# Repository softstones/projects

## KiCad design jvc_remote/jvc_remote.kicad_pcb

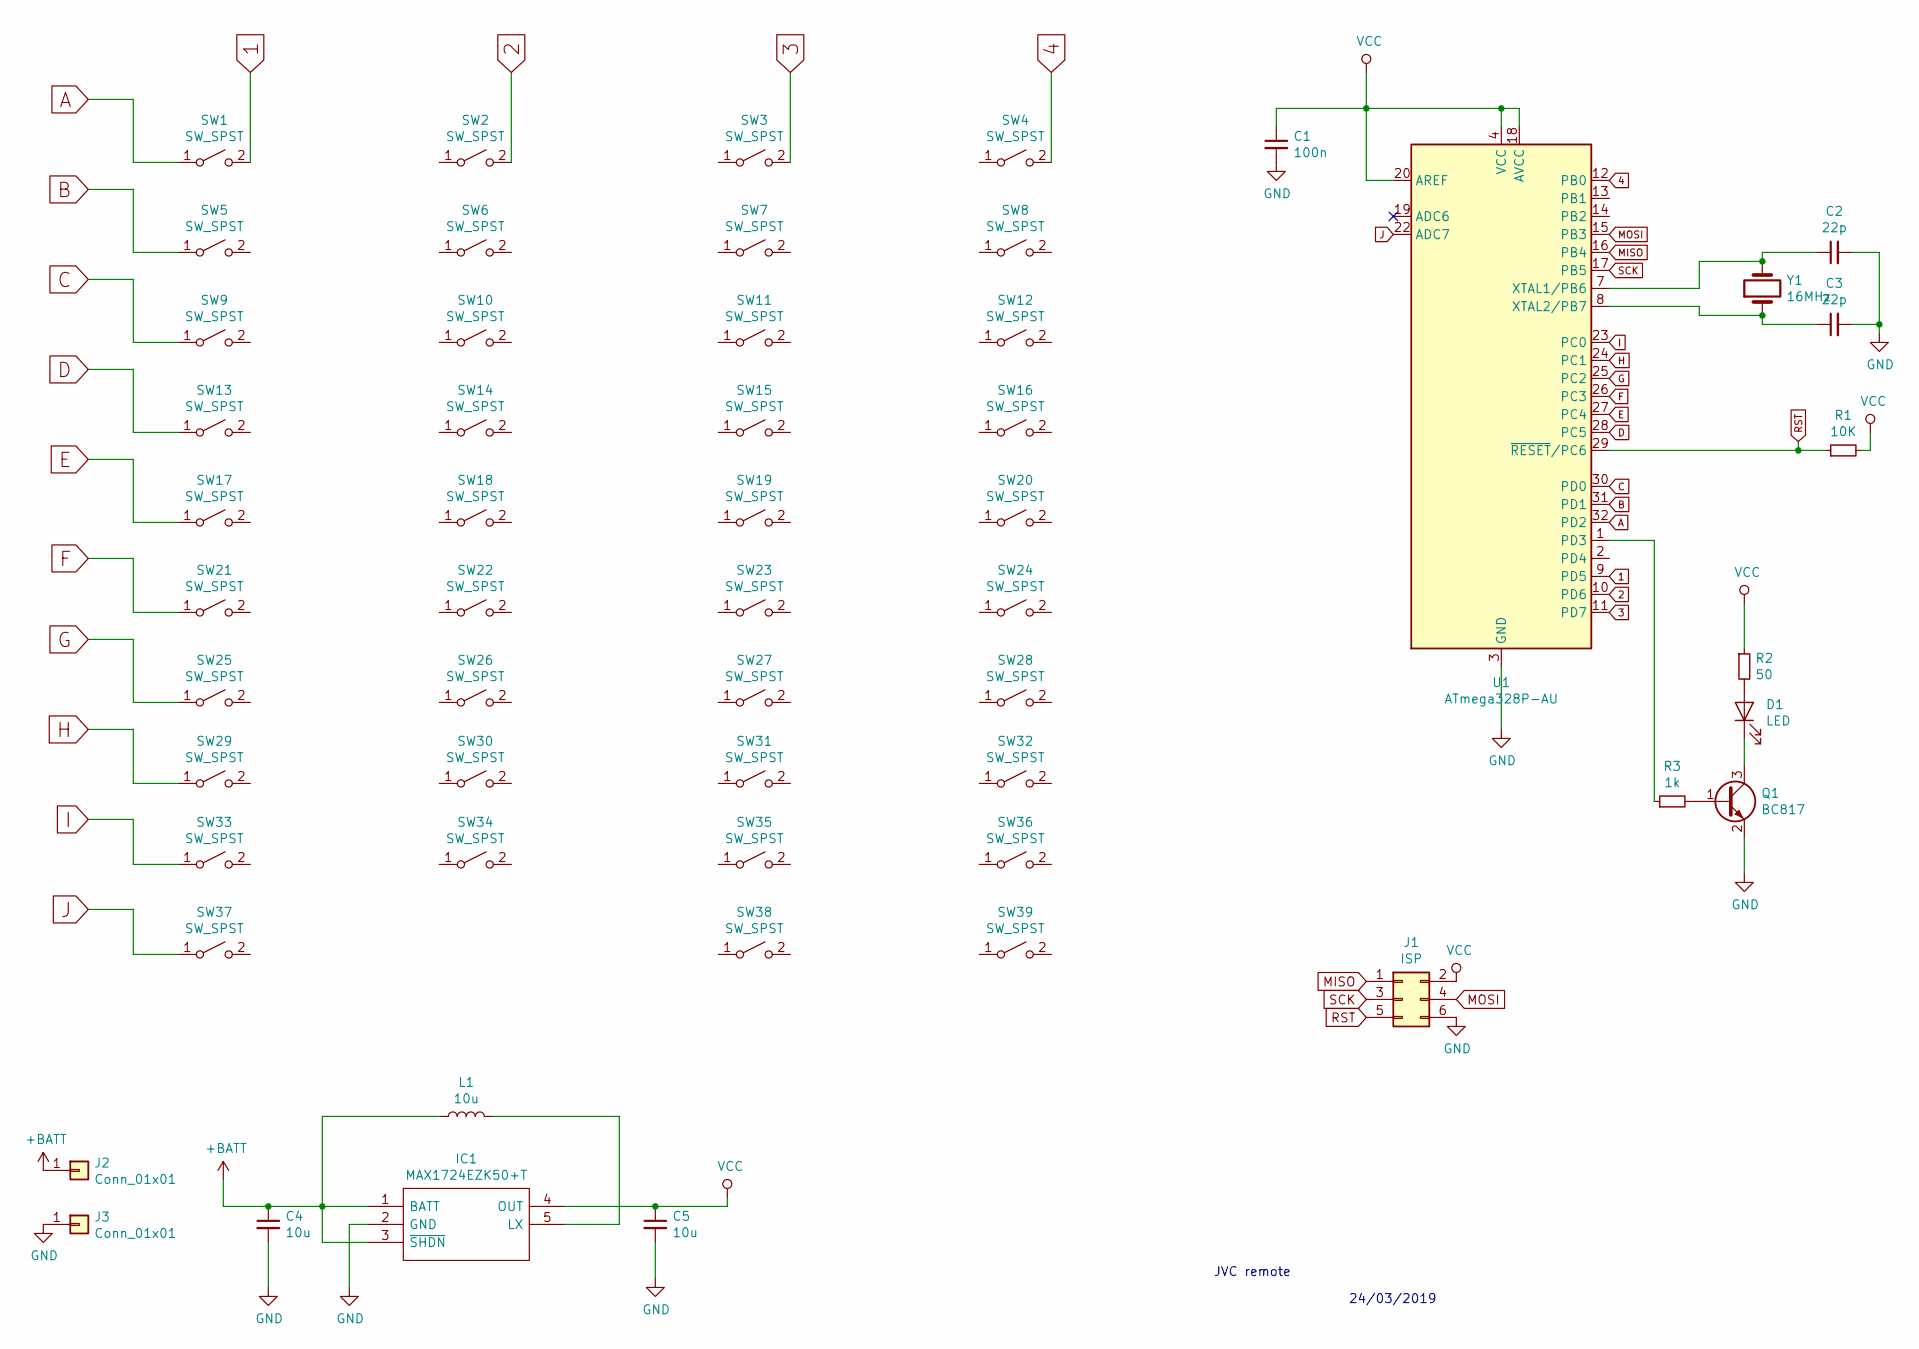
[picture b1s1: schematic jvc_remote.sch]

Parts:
C1: 100n; C_1206_HandSoldering
C2, C3: 22p; C_1206_HandSoldering
C4, C5: 10u; C_1206_HandSoldering
D1: LED; LED_D3.0mm_Horizontal_O1.27mm_Z2.0mm
IC1: MAX1724EZK50+T; SOT95P275X110-5N; Manufacturer_Part_Number MAX1724EZK50+T; Mouser Part Number 700-MAX1724EZK50T
J1: ISP; Pin_Header_Straight_2x03_Pitch2.54mm_SMD
J2, J3: Conn_01x01; Pin_Header_Straight_1x01_Pitch2.54mm
L1: 10u; SRN3015
Q1: BC817; SOT-23_Handsoldering_rotated
R1: 10K; R_1206_HandSoldering
R2: 50; R_1206_HandSoldering
R3: 1k; R_1206_HandSoldering
SW1, SW2, SW3, SW4, SW5, SW6, SW7, SW8, SW9, SW10, SW11, SW12, SW13, SW14, SW15, SW16, SW17, SW18, SW19, SW20, SW21, SW22, SW23, SW24, SW25, SW26, SW27, SW28, SW29, SW30, SW31, SW32, SW33, SW34, SW35, SW36, SW37, SW38, SW39: SW_SPST; SW_SPST_SKQG_4PINS
U1: ATmega328P-AU; QFP80P900X900X120-32N
Y1: 16MHz; ABLS

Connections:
1: SW1.2 (B), U1.9 (PD5)
2: SW2.2 (B), U1.10 (PD6)
3: SW3.2 (B), U1.11 (PD7)
4: SW4.2 (B), U1.12 (PB0)
+BATT: C4.1, IC1.1 (BATT), IC1.3 (~SHDN), J2.1, L1.1
A: SW1.1 (A), U1.32 (PD2)
B: SW5.1 (A), U1.31 (PD1)
C: SW9.1 (A), U1.30 (PD0)
D: SW13.1 (A), U1.28 (PC5)
E: SW17.1 (A), U1.27 (PC4)
F: SW21.1 (A), U1.26 (PC3)
G: SW25.1 (A), U1.25 (PC2)
GND: C1.2, C2.2, C3.2, C4.2, C5.2, IC1.2 (GND), J1.6, J3.1, Q1.2 (E), U1.3 (GND), U1.5 (GND), U1.21 (GND)
H: SW29.1 (A), U1.24 (PC1)
I: SW33.1 (A), U1.23 (PC0)
J: SW37.1 (A), U1.22 (ADC7)
MISO: J1.1, U1.16 (PB4)
MOSI: J1.4, U1.15 (PB3)
unnamed: C2.1, U1.7 (XTAL1/PB6), Y1.2
unnamed: C3.1, U1.8 (XTAL2/PB7), Y1.1
unnamed: D1.1 (K), Q1.3 (C)
unnamed: D1.2 (A), R2.2
unnamed: IC1.5 (LX), L1.2
unnamed: Q1.1 (B), R3.2
unnamed: R3.1, U1.1 (PD3)
RST: J1.5, R1.1, U1.29 (~RESET~/PC6)
SCK: J1.3, U1.17 (PB5)
VCC: C1.1, C5.1, IC1.4 (OUT), J1.2, R1.2, R2.1, U1.4 (VCC), U1.6 (VCC), U1.18 (AVCC), U1.20 (AREF)

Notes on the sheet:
JVC remote
24/03/2019

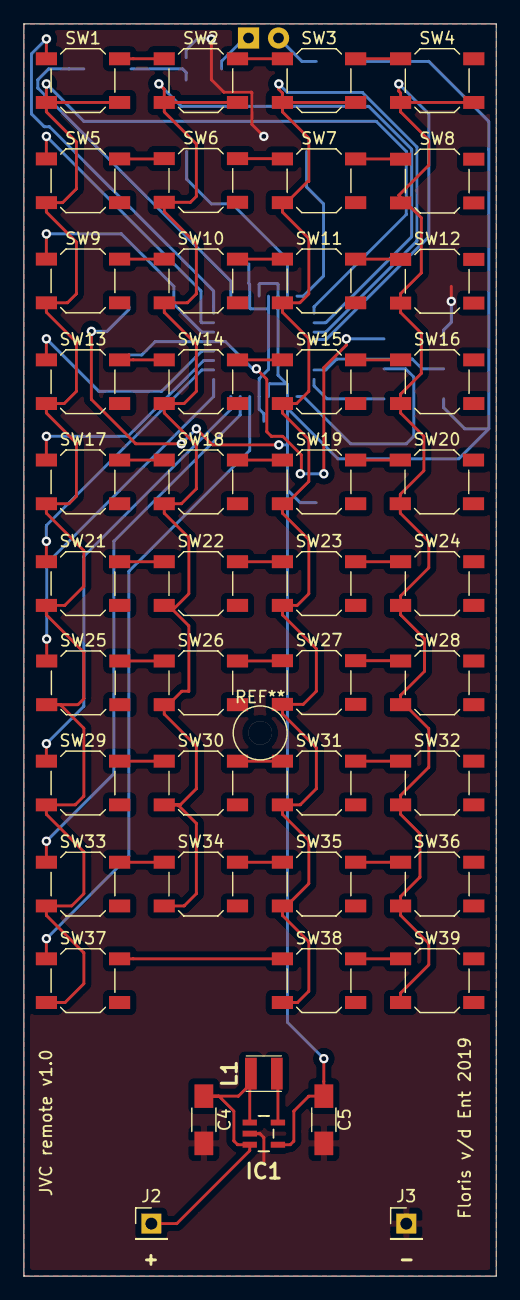
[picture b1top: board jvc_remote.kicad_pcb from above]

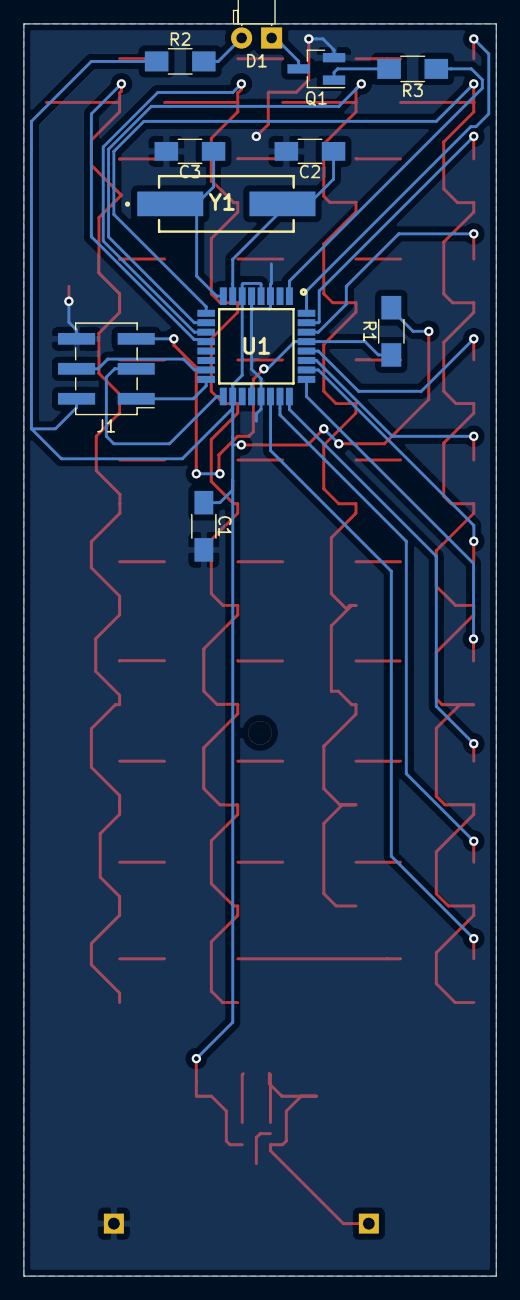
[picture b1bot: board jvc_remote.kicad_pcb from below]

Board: 2 copper layers, 40.0 x 106.0 mm, 56 parts (11 on the bottom side), 28 nets.

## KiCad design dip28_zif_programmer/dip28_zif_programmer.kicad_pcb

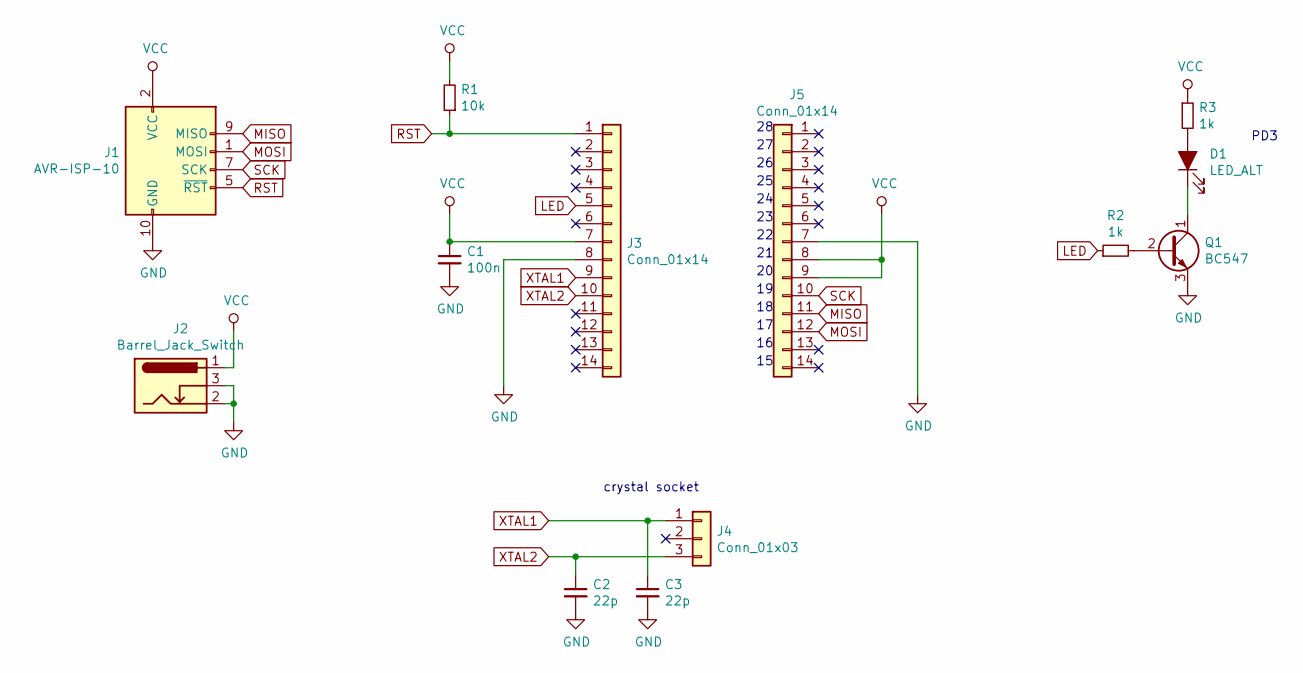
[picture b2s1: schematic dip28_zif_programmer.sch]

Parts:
C1: 100n; C_Disc_D5.0mm_W2.5mm_P2.50mm
C2, C3: 22p; C_Disc_D5.0mm_W2.5mm_P2.50mm
D1: LED_ALT; LED_D5.0mm
J1: AVR-ISP-10; Pin_Header_Straight_2x05_Pitch2.54mm
J2: Barrel_Jack_Switch; BARREL_JACK
J3, J5: Conn_01x14; PinHeader_1x14_P2.54mm_Vertical
J4: Conn_01x03; PinHeader_1x03_P2.54mm_Vertical
Q1: BC547; TO-92_Molded_Narrow
R1: 10k; R_Axial_DIN0207_L6.3mm_D2.5mm_P7.62mm_Horizontal
R2, R3: 1k; R_Axial_DIN0207_L6.3mm_D2.5mm_P7.62mm_Horizontal

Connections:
GND: C1.2, C2.2, C3.2, J1.4 (GND), J1.6 (GND), J1.8 (GND), J1.10 (GND), J2.2, J2.3, J3.8, J5.7, Q1.3 (E)
LED: J3.5, R2.1
MISO: J1.9 (MISO), J5.11
MOSI: J1.1 (MOSI), J5.12
unnamed: D1.1 (K), Q1.1 (C)
unnamed: D1.2 (A), R3.2
unnamed: Q1.2 (B), R2.2
RST: J1.5 (~RST), J3.1, R1.1
SCK: J1.7 (SCK), J5.10
VCC: C1.1, J1.2 (VCC), J2.1, J3.7, J5.8, J5.9, R1.2, R3.1
XTAL1: C3.1, J3.9, J4.1
XTAL2: C2.1, J3.10, J4.3

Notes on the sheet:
PD3
crystal socket

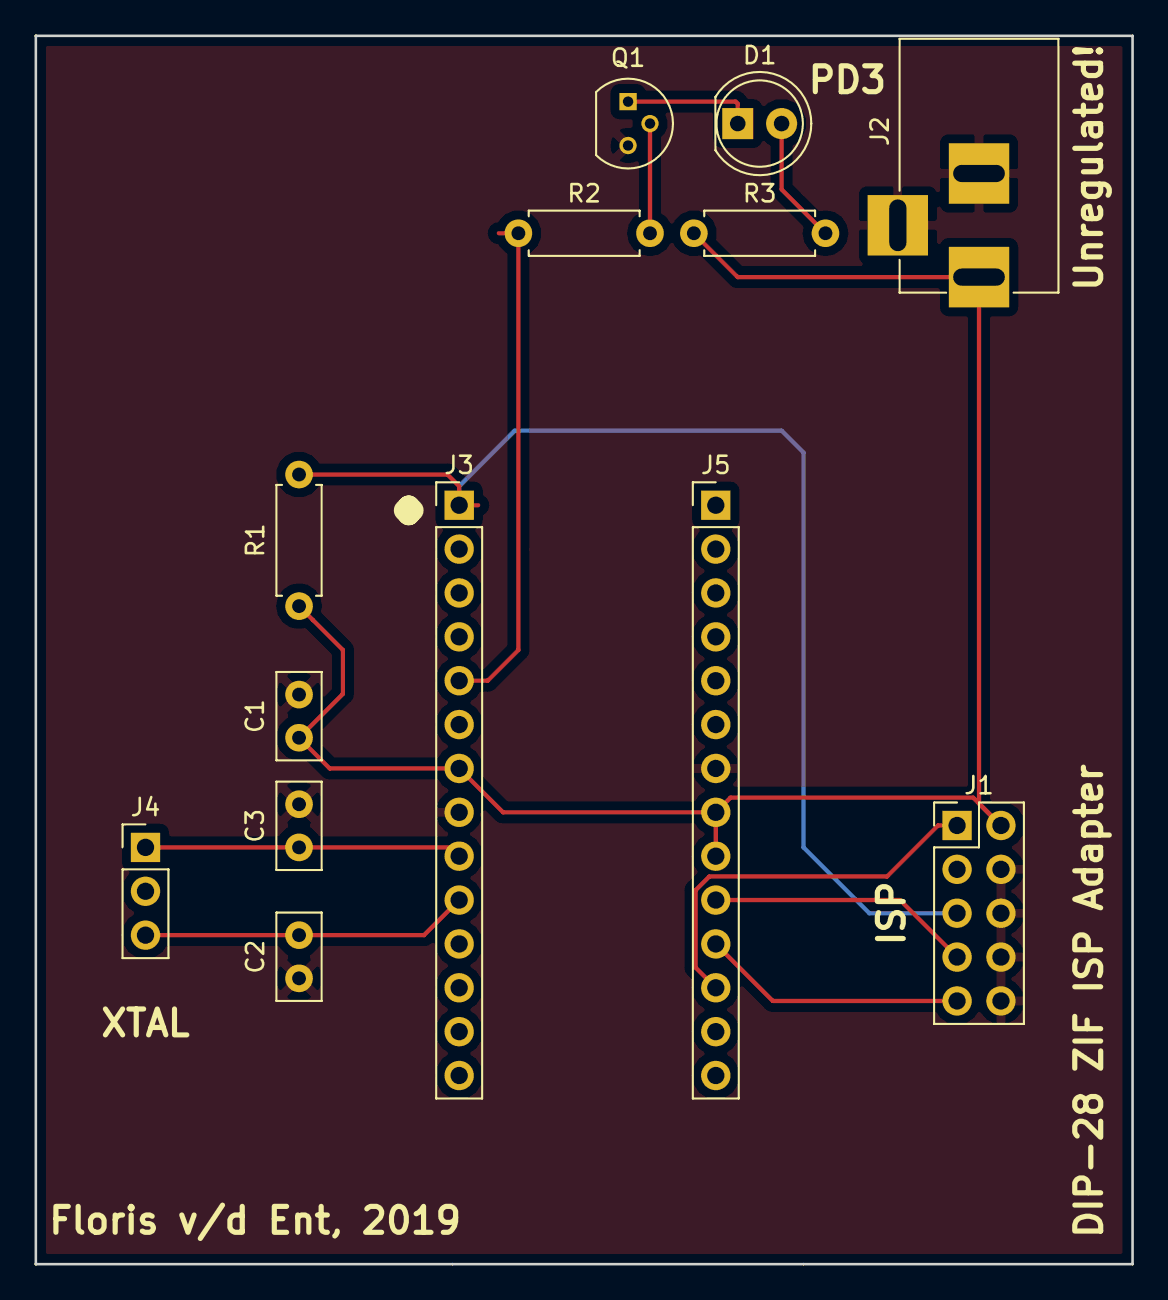
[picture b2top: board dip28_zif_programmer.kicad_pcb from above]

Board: 2 copper layers, 63.5 x 71.1 mm, 13 parts (0 on the bottom side), 12 nets.

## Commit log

2020-09-08 helo world begin
